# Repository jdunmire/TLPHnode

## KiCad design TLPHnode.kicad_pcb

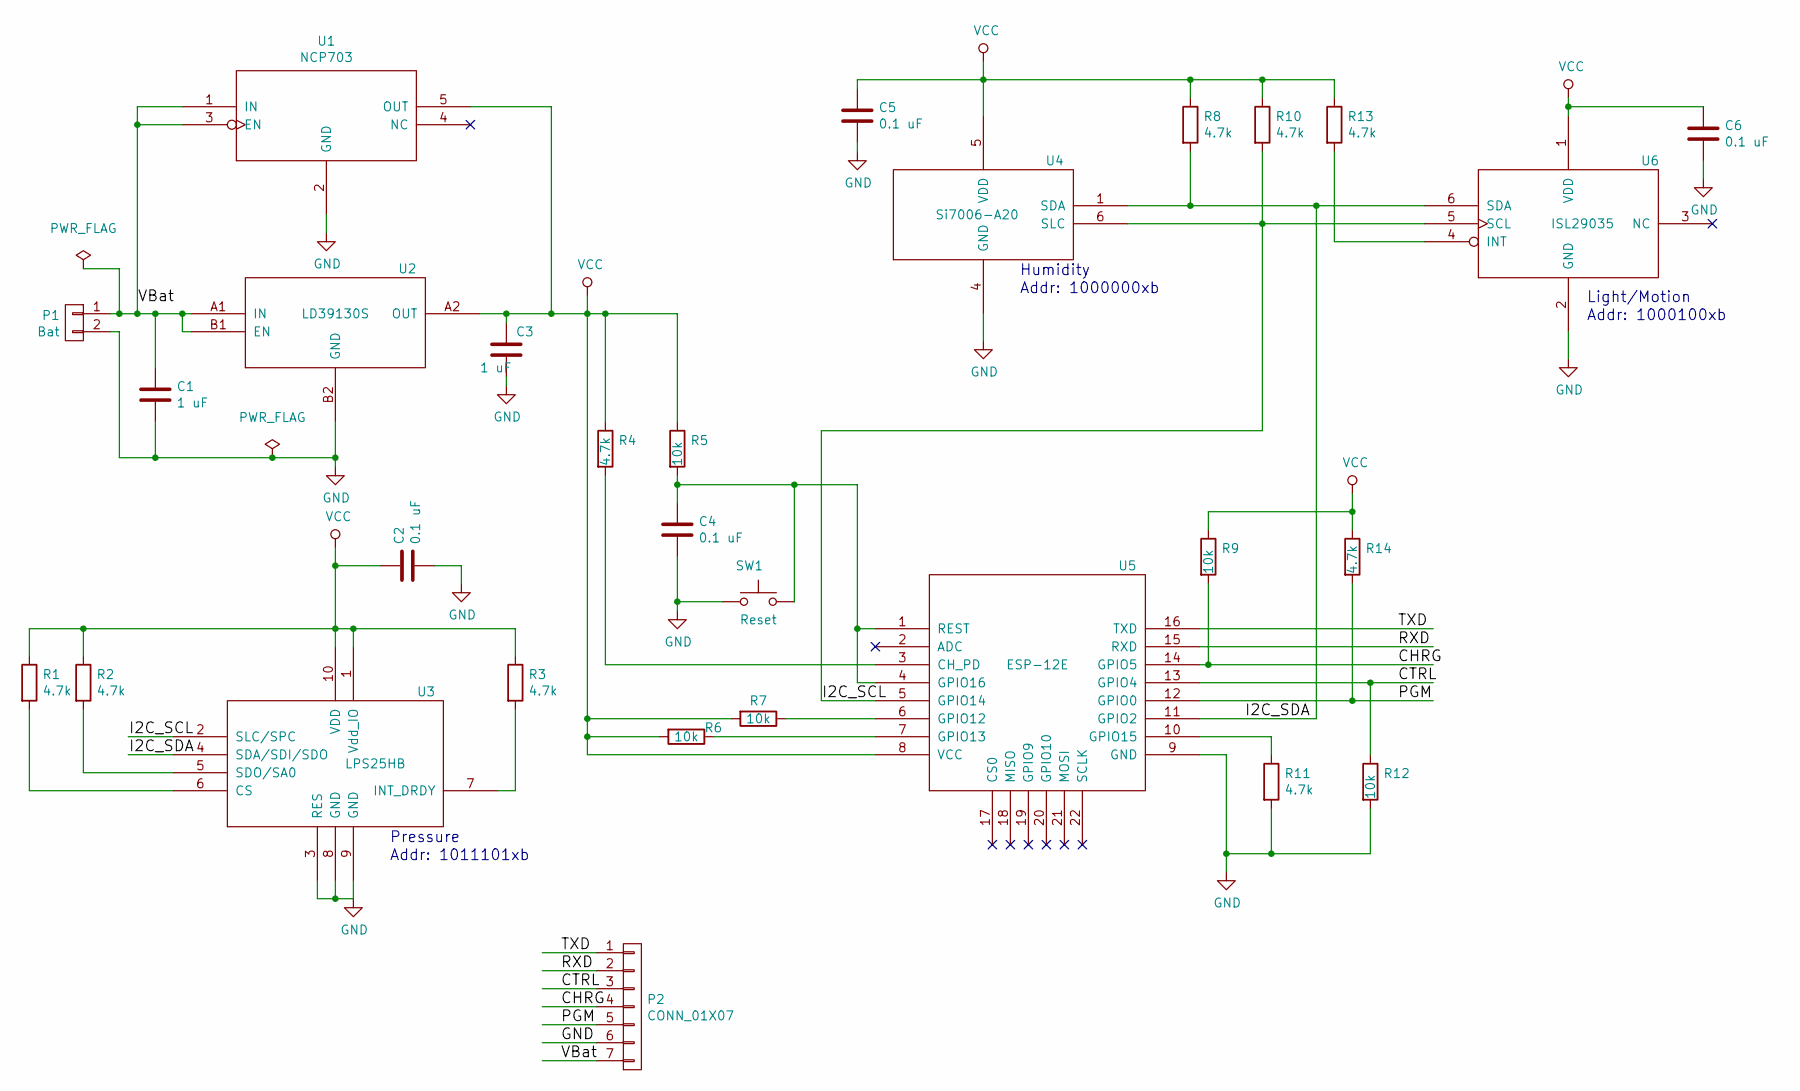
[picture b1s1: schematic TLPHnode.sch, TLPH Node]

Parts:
C1, C3: 1 uF; C_0603
C2, C4, C5, C6: 0.1 uF; C_0603
P1: Bat; Pin_Header_Straight_1x02
P2: CONN_01X07; FPC_conn-7_8x4.9mm_Pitch0.5mm
R1, R2, R3, R4, R8, R10, R11, R13, R14: 4.7k; R_0603
R5, R6, R7, R9, R12: 10k; R_0603
SW1: Reset; ESwitch-SMD-4
U1: NCP703; NCP703-TSOP-5
U2: LD39130S; LD39130S-FlipChip-4
U3: LPS25HB; LPS25HB-HLGA-10L-2.5x2.5mm
U4: Si7006-A20; Si7006_A20-DFN-6
U5: ESP-12E
U6: ISL29035; ISL29035-DFN-6-1.5x1.6mm_Pitch0.5mm

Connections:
/CHRG: P2.4, R9.2, U5.14 (GPIO5)
/CTRL: P2.3, R12.1, U5.13 (GPIO4)
/I2C_SCL: R10.2, U3.2 (SLC/SPC), U4.6 (SLC), U5.5 (GPIO14), U6.5 (SCL)
/I2C_SDA: R8.2, U3.4 (SDA/SDI/SDO), U4.1 (SDA), U5.11 (GPIO2), U6.6 (SDA)
/PGM: P2.5, R14.2, U5.12 (GPIO0)
/RXD: P2.2, U5.15 (RXD)
/TXD: P2.1, U5.16 (TXD)
/VBat: C1.1, P1.1, P2.7, U1.1 (IN), U1.3 (EN), U2.A1 (IN), U2.B1 (EN)
GND: C1.2, C2.2, C3.2, C4.2, C5.2, C6.2, P1.2, P2.6, R11.2, R12.2, SW1.1, U1.2 (GND), U2.B2 (GND), U3.3 (RES), U3.8 (GND), U3.9 (GND), U4.4 (GND), U5.9 (GND), U6.2 (GND)
unnamed: C4.1, R5.2, SW1.2, U5.1 (REST), U5.4 (GPIO16)
unnamed: R1.2, U3.6 (CS)
unnamed: R2.2, U3.5 (SDO/SA0)
unnamed: R3.2, U3.7 (INT_DRDY)
unnamed: R4.2, U5.3 (CH_PD)
unnamed: R6.1, U5.7 (GPIO13)
unnamed: R7.1, U5.6 (GPIO12)
unnamed: R11.1, U5.10 (GPIO15)
unnamed: R13.2, U6.4 (INT)
VCC: C2.1, C3.1, C5.1, C6.1, R1.1, R2.1, R3.1, R4.1, R5.1, R6.2, R7.2, R8.1, R9.1, R10.1, R13.1, R14.1, U1.5 (OUT), U2.A2 (OUT), U3.1 (Vdd_IO), U3.10 (VDD), U4.5 (VDD), U5.8 (VCC), U6.1 (VDD)

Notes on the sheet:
Pressure
Light/Motion
Humidity
Addr: 1011101xb
Addr: 1000000xb
Addr: 1000100xb

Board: 4 copper layers, 30 parts (3 on the bottom side), 19 nets, no tracks yet.

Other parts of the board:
Ref**: RockingDLogo_9x7

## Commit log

2016-01-29 Starting point
    On branch master
    new file: .gitignore
    new file: LICENSE.txt
    new file: PRODUCT.txt
    new file: README.md
    new file: cern_ohl_v_1_2_howto.pdf
2016-01-29 Add CAM and changes file
    On branch master
    new file: CAM/.gitignore
    new file: CAM/README.md
    new file: CHANGES.txt
2016-01-29 Add my title block and frame
    On branch master
    new file: rockingdlabs_letter_with_logo.kicad_wks
2016-01-29 Add initial KiCad project files
    Files created by 'New Project'
2016-01-29 Added title block
    On branch master
    new file: TLPHnode-cache.lib
    modified: TLPHnode.pro
    modified: TLPHnode.sch
2016-02-02 Add datasheet for jumper cable
    On branch master
    modified: datasheets/getdatasheets.sh
2016-02-02 Typo
    On branch master
    modified: datasheets/README.md
2016-11-27 Add linear regulators and battery chargers
    On branch master
    modified: datasheets/getdatasheets.sh
2016-12-06 Check-point: ESP-12E with two voltage regulators
    Initial attempts at a layout show that I should use the ESP-12 footprint
    to avoid pads for the extra connections on the end of the ESP-12E.
    modified: TLPHnode-cache.lib
    modified: TLPHnode.pro
    modified: TLPHnode.sch
2016-12-06 Add datasheet for battery connector.
    modified: datasheets/getdatasheets.sh
2016-12-06 Use JST PH footprint for battery
    modified: TLPHnode.sch
2016-12-06 Ignore datasheets with upper case suffixes
    modified: datasheets/.gitignore
2016-12-06 Checkpoint before moving to kicad-rockingdlabs library
2016-12-07 Adjust paths for unified rockingdlabs library
    On branch master
    modified: TLPHnode-cache.lib
    modified: TLPHnode.kicad_pcb
    modified: TLPHnode.pro
    modified: TLPHnode.sch
2016-12-07 Clarify labels
    Id->Sheet
    Sheet->Path
    On branch master
    modified: rockingdlabs_letter_with_logo.kicad_wks
2016-12-09 Add 5pin connector
2016-12-09 Check-point
    - some parts tentatively placed
    - commiting before adding any traces
    - design rules set. OSH 4-layer
    On branch master
    modified: TLPHnode-cache.lib
    modified: TLPHnode.kicad_pcb
2016-12-09 Check-point: First placement
2016-12-09 Check-point: 28x20.5mm board
    - Only ESP-12E and power connector on the back
2016-12-10 Fix connection
    On branch master
    modified: TLPHnode.sch
2016-12-10 Check-point: layout passes DRM, References visible
    On branch master
    modified: TLPHnode-cache.lib
    modified: TLPHnode.kicad_pcb
2016-12-10 Add copyright notice, partname and date
    On branch master
    modified: TLPHnode.kicad_pcb
2016-12-10 Add Logo
    On branch master
    modified: TLPHnode.kicad_pcb
2016-12-12 Change Bat to a through-hole connector
    - Add VBat to P2 so that a single connector can
    be used when connecting to a charger/breakout/debug board
    - Use a two-pin through-hole header for VBat to make it
    easy to solder wires rather than use a connector.
    On branch AltPower
    modified: TLPHnode-cache.lib
2016-12-15 Change battery connection to bare pads
    - Use pin model rather than socket
    - remove 3d model
2016-12-21 Add notes file
    On branch AltPower
    new file: NOTES.txt
2016-12-21 Set grid and drill origin point
    On branch AltPower
    modified: TLPHnode.kicad_pcb
2016-12-24 Add Charger control signals to P2
    - All routes removed.
    On branch addChrgCtrl
    modified: TLPHnode-cache.lib
    modified: TLPHnode.kicad_pcb
    modified: TLPHnode.net
    modified: TLPHnode.sch
2016-12-28 Checkpoint - Routing complete, 7-pin P2
    - Includes control and monitoring signals for battery charger
    On branch addChrgCtrl
    modified: TLPHnode.kicad_pcb
    modified: TLPHnode.net
    modified: TLPHnode.sch

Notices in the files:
TLPHnode.kicad_pcb:
Copyright 2016 J. Dunmire, All Rights Reserved
